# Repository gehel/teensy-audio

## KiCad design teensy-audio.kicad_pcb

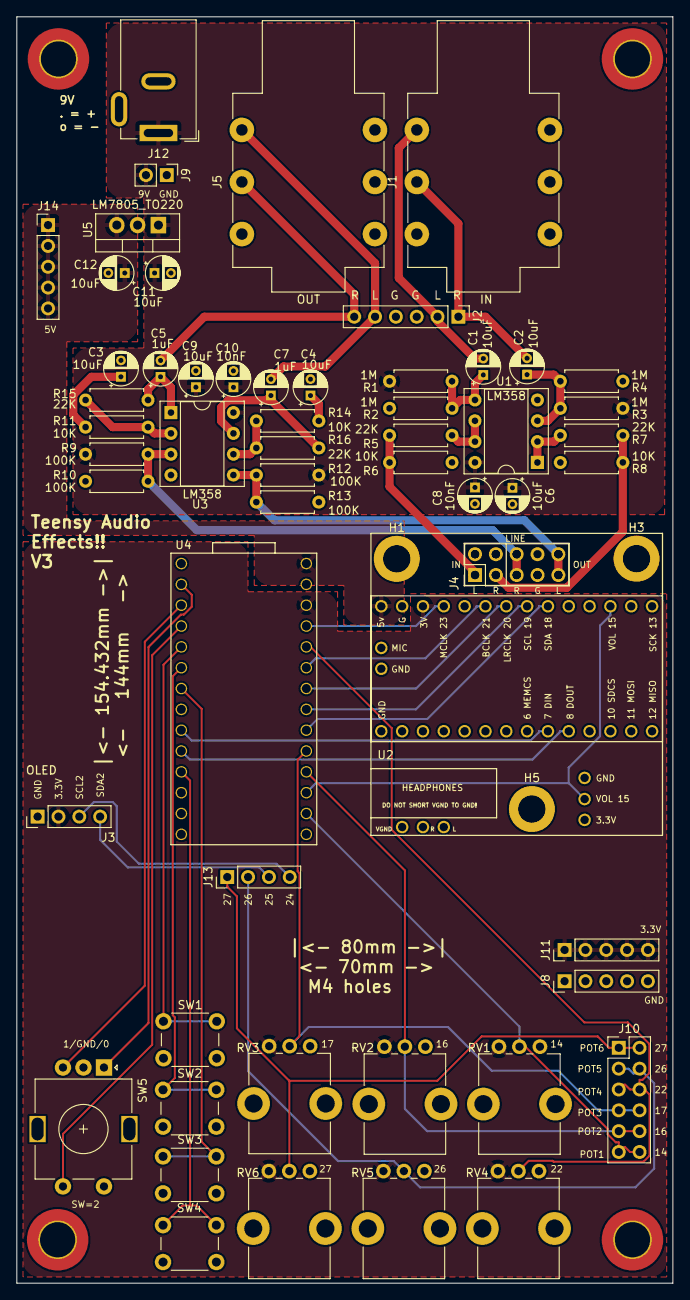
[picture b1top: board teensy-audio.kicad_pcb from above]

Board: 2 copper layers, 80.0 x 154.4 mm, 63 parts (0 on the bottom side), 46 nets.

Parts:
C1, C2, C3, C4, C6, C9, C11, C12: 10uF; CP_Radial_D4.0mm_P2.00mm
C5, C7: 1uF; CP_Radial_D4.0mm_P2.00mm
C8, C10: 10nF; CP_Radial_D4.0mm_P2.00mm
H1, H3, H5: MountingHole_Pad; MountingHole_3.2mm_M3_DIN965_Pad_TopBottom
H2, H4, H6, H7: MountingHole_Pad; MountingHole_4.3mm_M4_DIN965_Pad_TopBottom
J1, J5: AudioJack3; Jack_6.35mm_Neutrik_NMJ6HFD2-AU_Horizontal
J2: Conn_01x06; PinHeader_1x06_P2.54mm_Vertical
J3, J13: Conn_01x04; PinHeader_1x04_P2.54mm_Vertical
J4: Conn_02x05_Odd_Even; PinHeader_2x05_P2.54mm_Vertical
J8, J11, J14: Conn_01x05; PinHeader_1x05_P2.54mm_Vertical
J9: Conn_01x02; PinHeader_1x02_P2.54mm_Vertical
J10: Conn_02x06_Odd_Even; PinHeader_2x06_P2.54mm_Vertical
J12: Barrel_Jack; BarrelJack_GCT_DCJ200-10-A_Horizontal
R1, R2, R3, R4: 1M; R_Axial_DIN0207_L6.3mm_D2.5mm_P7.62mm_Horizontal
R5, R7, R15, R16: 22K; R_Axial_DIN0207_L6.3mm_D2.5mm_P7.62mm_Horizontal
R6, R8, R11, R14: 10K; R_Axial_DIN0207_L6.3mm_D2.5mm_P7.62mm_Horizontal
R9, R10, R12, R13: 100K; R_Axial_DIN0207_L6.3mm_D2.5mm_P7.62mm_Horizontal
RV1, RV2, RV3, RV4, RV5, RV6: 10K; Potentiometer_Bourns_PTV09A-1_Single_Vertical
SW1, SW2, SW3, SW4: SW_Push; SW_PUSH_6mm
SW5: RotaryEncoder_Switch; RotaryEncoder_Alps_EC11E-Switch_Vertical_H20mm
U1, U3: LM358; DIP-8_W7.62mm_Socket
U2: Teensy4.0_AudioShield_REVD; 4.0audioshield
U4: Teensy4.0; Teensy40_SMT
U5: LM7805_TO220; TO-220-3_Vertical

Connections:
+3.3V: J3.2, J11.1, J11.2, J11.3, J11.4, J11.5, RV1.1, RV2.1, RV3.1, RV4.1, RV5.1, RV6.1, U2.28 (3V), U4.31 (3V3)
+5V: C12.1, J14.1, J14.2, J14.3, J14.4, J14.5, U2.30 (5V), U4.33 (VIN), U5.3 (VO)
BCLK: U2.25 (21_A7_RX5_BCLK1), U4.28 (21_A7_RX5_BCLK1)
DIN: U2.9 (7_RX2_OUT1A), U4.9 (7_RX2_OUT1A)
DOUT: U2.10 (8_TX2_IN1), U4.10 (8_TX2_IN1)
ENC_A: SW5.A, U4.2 (0_RX1_CRX2_CS1)
ENC_B: SW5.B, U4.3 (1_TX1_CTX2_MISO1)
ENC_SW: SW5.S1, U4.4 (2_OUT2)
GND: C11.2, C12.2, H1.1, H2.1, H3.1, H4.1, H5.1, H6.1, H7.1, J3.1, J8.1, J8.2, J8.3, J8.4, J8.5, J9.1, J12.2, RV1.3, RV2.3, RV3.3, RV4.3, RV5.3, RV6.3, SW1.2, SW2.2, SW3.1, SW4.1, SW5.C, SW5.S2, U2.1 (GND), U2.29 (GND), U4.1 (GND), U4.32 (GND), U5.2 (GND)
GNDA: C3.2, C4.2, C6.2, C8.2, C9.2, C10.2, J1.T, J2.3, J2.4, J4.2, J4.4, J4.7, J5.T, R2.2, R4.2, R6.2, R8.2, R10.2, R13.2, U1.4 (V-), U2.32 (LINE_OUT_GND), U2.36 (LINE_IN_R_GND), U2.37 (LINE_IN_L_GND), U3.4 (V-)
JACK_IN_L: C1.2, J1.S, J2.2
JACK_IN_R: C2.2, J1.R, J2.1
JACK_OUT_L: C7.2, J2.5, J5.S
JACK_OUT_R: C5.2, J2.6, J5.R
LINE_IN_L: J4.1, R5.2, R6.1, U2.35 (LINE_IN_L)
LINE_IN_R: J4.3, R7.2, R8.1, U2.34 (LINE_IN_R)
LINE_OUT_L: J4.9, J4.10, R12.2, R13.1, U2.31 (LINE_OUT_L), U2.46, U3.5 (+)
LINE_OUT_R: J4.5, J4.6, R9.2, R10.1, U2.33 (LINE_OUT_R), U2.45, U3.3 (+)
LRCLK: U2.24 (20_A6_TX5_LRCLK1), U4.27 (20_A6_TX5_LRCLK1)
MCLK: U2.27 (23_A9_CRX1_MCLK1), U4.30 (23_A9_CRX1_MCLK1)
unnamed: C3.1, R11.2
unnamed: C4.1, R14.2
unnamed: C5.1, R15.2, U3.1
unnamed: C7.1, R16.2, U3.7
unnamed: C2.1, R3.2, R4.1, U1.3 (+)
unnamed: R7.1, U1.1, U1.2 (-)
unnamed: C1.1, R1.2, R2.1, U1.5 (+)
unnamed: R5.1, U1.6 (-), U1.7
unnamed: R11.1, R15.1, U3.2 (-)
unnamed: R14.1, R16.1, U3.6 (-)
POT1: J10.11, J10.12, RV1.2, U4.21 (14_A0_TX3_SPDIF_OUT)
POT2: J10.9, J10.10, RV2.2, U4.23 (16_A2_RX4_SCL1)
POT3: J10.7, J10.8, RV3.2, U4.24 (17_A3_TX4_SDA1)
POT4: J10.5, J10.6, RV4.2, U4.29 (22_A8_CTX1)
POT5: J10.3, J10.4, J13.2, RV5.2
POT6: J10.1, J10.2, J13.1, RV6.2
SCL: U2.23 (19_A5_SCL0), U4.26 (19_A5_SCL0)
SCL2: J3.3, J13.4
SDA: U2.22 (18_A4_SDA0), U4.25 (18_A4_SDA0)
SDA2: J3.4, J13.3
SW2: SW1.1, U4.5 (3_LRCLK2)
SW3: SW2.1, U4.6 (4_BCLK2)
SW4: SW3.2, U4.7 (5_IN2)
SW5: SW4.2, U4.11 (9_OUT1C)
VCC: C6.1, C8.1, C9.1, C10.1, C11.1, J9.2, J12.1, R1.1, R3.1, R9.1, R12.1, U1.8 (V+), U3.8 (V+), U5.1 (VI)
VOL: U2.19 (15_A1_RX3_SPDIF_IN_VOL), U2.39 (VOL_15_A1), U4.22 (15_A1_RX3_SPDIF_IN)

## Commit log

2023-06-13 added power connectors
2023-06-19 finished pcb
2023-06-26 minor
2023-06-28 added input power pins
2023-06-28 added board dimensions to silkscreen
2023-06-28 added pin nubmers to silkscreen
2023-07-16 removed bridged ground plane
2023-07-17 minor routing simplification
2023-07-17 added TODO file
2023-08-02 added oled screen
2023-08-02 switch inputs and outputs positions on pcb
2023-08-02 silkscreen cleanup
2023-08-02 split audio and digital grounds
2023-08-02 decoupling capacitor for audio opamp
2023-08-02 more space for oled display
2023-08-03 corrected barrel plug
2023-08-16 stereo input and output
2023-08-18 do not stack teensy and teensy audio
2023-08-31 cleanup of PCB (cosmetic)
2023-09-10 fix broken digital ground
